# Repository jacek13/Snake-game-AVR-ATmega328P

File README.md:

# **Snake game on AVR**

The aim of my project was to create a device that allows you to play the popular game `"Snake"`. I completed the project as part of a university subject. While creating it, I used my original snake game written in C++ for Windows (graphics shown in the command line). I was prototyping the Arduino version. Then I rewritten the whole project into C language on the AVR microcontroller (ATmega328P). 

# **Game Demo**

# **Elements used in the project:**
* RGB matrix 8 x 8 WS2812B
* 5 microswitches
* Buzzer HCM1206X
* ATmega328P
* USB as power supply
* custom board (All eagle files is in resources folder)
* necessary RC elements (all information about values ​​is in the schematics)

# **PCB**

# **IMPORTANT**

in the resources folder there are hex files for both versions of the project (Arduino and AVR). Please note that the AVR version only works for frequencies based on the internal RC oscillator (Set fuse bits on 8Mhz). The prototype version from arduino uses an external crystal oscillator (then you have to change the fuse bits to the external 16 MHz clock). This limitation is due to the [**`light_ws2812`**](https://github.com/cpldcpu/light_ws2812) library that I am using in the project.

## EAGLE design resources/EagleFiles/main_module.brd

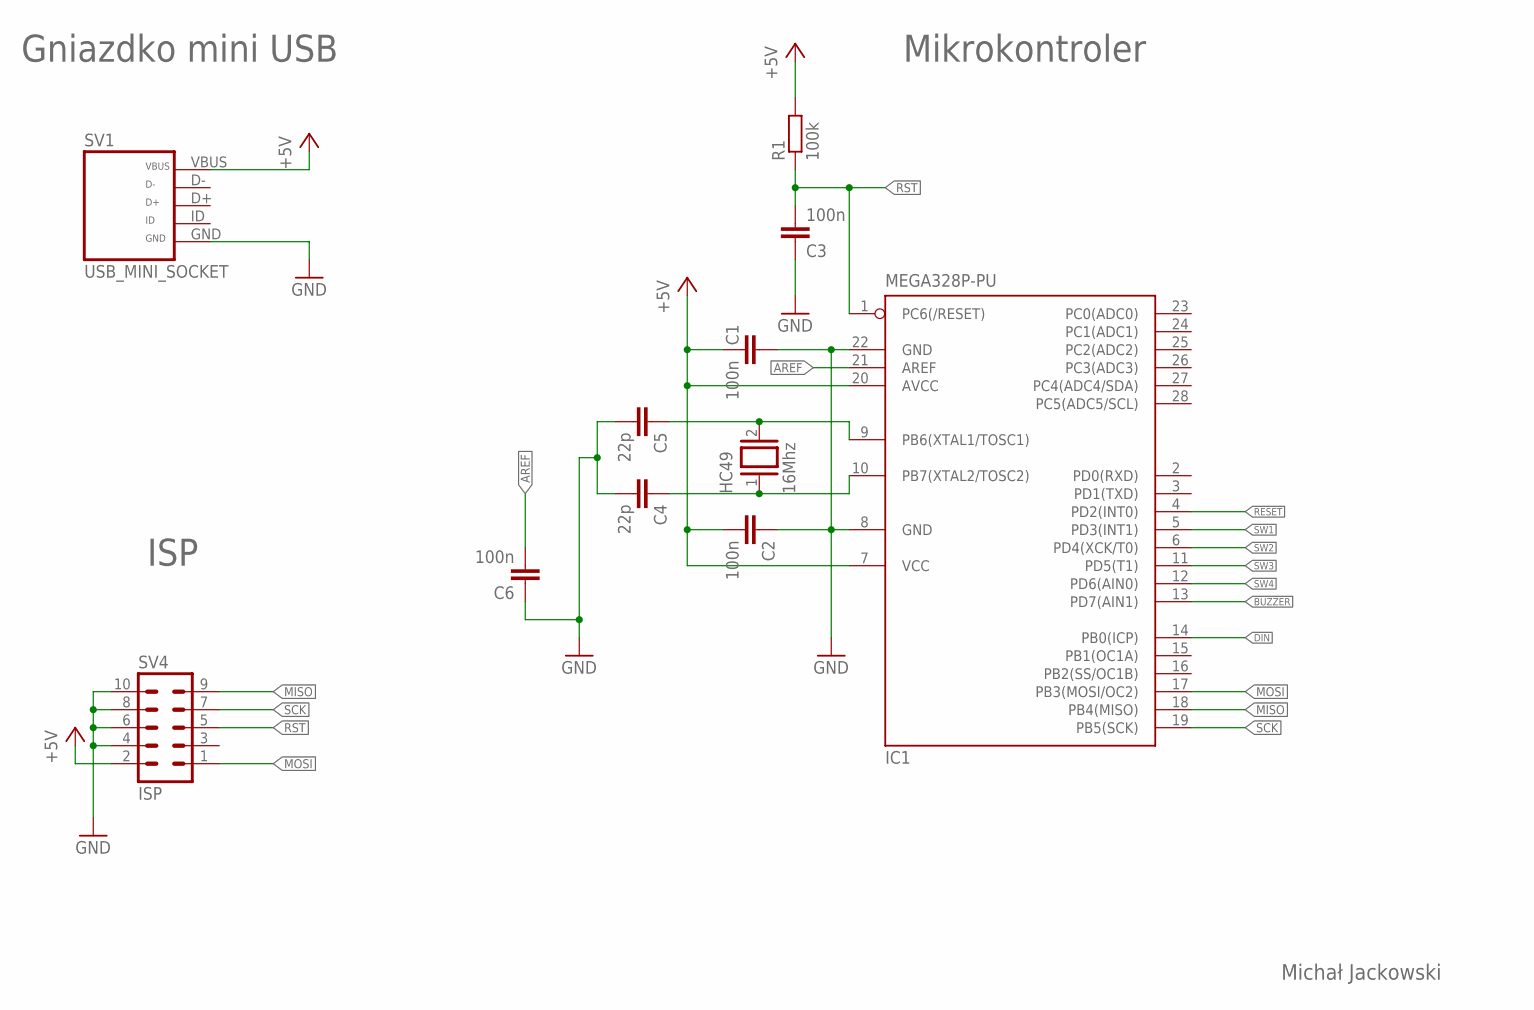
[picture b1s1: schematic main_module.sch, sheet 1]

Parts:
C1, C2, C3, C6: 100n; C025-040X050
C4, C5: 22p; C025-040X050
IC1: MEGA328P-PU; DIL28-3
Q1: 16Mhz; Q
R1: 100k; 0204/7
SV1: USB_MINI_SOCKET; FE05-1
SV4: ISP; ML10L

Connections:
+5V: C1.2, C2.2, IC1.7 (VCC), IC1.20 (AVCC), R1.2, SV1.VBUS, SV4.2; also elsewhere on the board
AREF: C6.2, IC1.21 (AREF)
BUZZER: IC1.13 (PD7(AIN1)); also elsewhere on the board
DIN: IC1.14 (PB0(ICP)); also elsewhere on the board
GND: C1.1, C2.1, C3.1, C4.2, C5.2, C6.1, IC1.8 (GND), IC1.22 (GND), SV1.GND, SV4.4, SV4.6, SV4.8, SV4.10; also elsewhere on the board
MISO: IC1.18 (PB4(MISO)), SV4.9
MOSI: IC1.17 (PB3(MOSI/OC2)), SV4.1
unnamed: C5.1, IC1.9 (PB6(XTAL1/TOSC1)), Q1.2
unnamed: C4.1, IC1.10 (PB7(XTAL2/TOSC2)), Q1.1
RESET: IC1.4 (PD2(INT0)); also elsewhere on the board
RST: C3.2, IC1.1 (PC6(/RESET)), R1.1, SV4.5
SCK: IC1.19 (PB5(SCK)), SV4.7
SW1: IC1.5 (PD3(INT1)); also elsewhere on the board
SW2: IC1.6 (PD4(XCK/T0)); also elsewhere on the board
SW3: IC1.11 (PD5(T1)); also elsewhere on the board
SW4: IC1.12 (PD6(AIN0)); also elsewhere on the board

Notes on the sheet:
Michał Jackowski
Gniazdko mini USB
ISP
Mikrokontroler

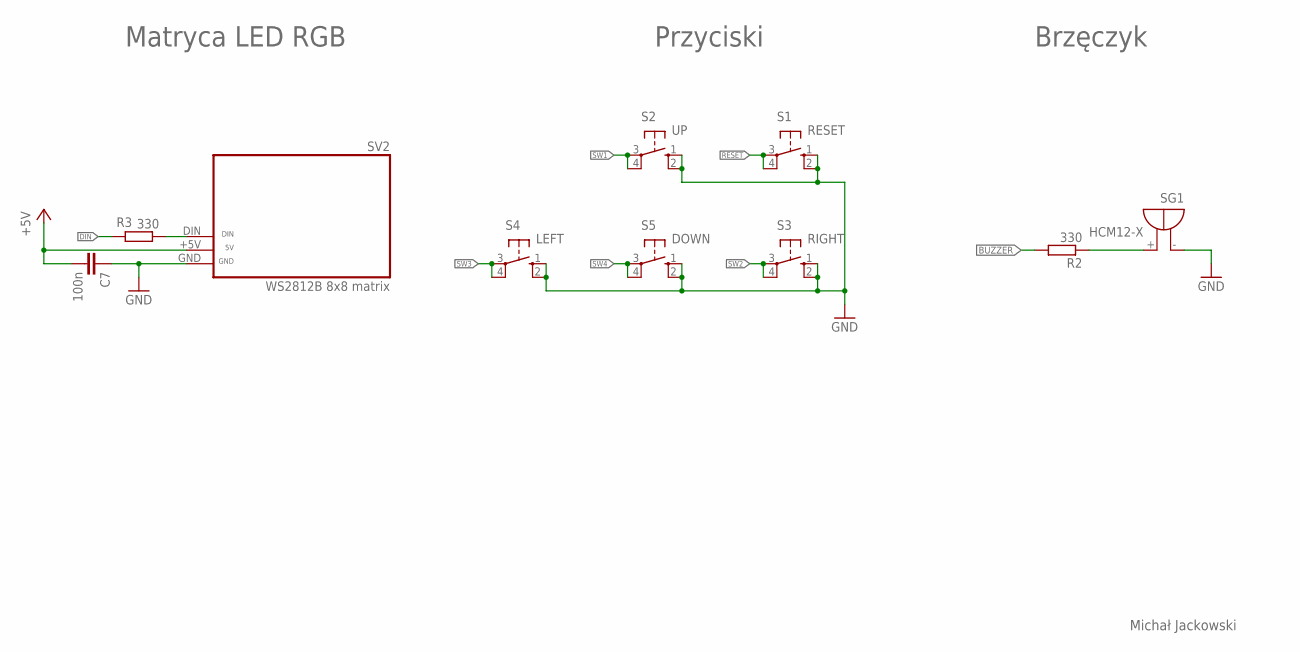
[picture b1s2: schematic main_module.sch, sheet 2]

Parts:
C7: 100n; C025-040X050
R2, R3: 330; 0204/7
S1: RESET; B3F-40XX
S2: UP; B3F-40XX
S3: RIGHT; B3F-40XX
S4: LEFT; B3F-40XX
S5: DOWN; B3F-40XX
SG1: HCM12-X; F/QMBIII
SV2: RGB_MATRIX_SOCKET; MA03-1

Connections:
+5V: C7.2, SV2.+5V (5V); also elsewhere on the board
BUZZER: R2.2; also elsewhere on the board
DIN: R3.2; also elsewhere on the board
GND: C7.1, S1.1 (S), S1.2 (S1), S2.1 (S), S2.2 (S1), S3.1 (S), S3.2 (S1), S4.1 (S), S4.2 (S1), S5.1 (S), S5.2 (S1), SG1.- (+), SV2.GND; also elsewhere on the board
unnamed: R2.1, SG1.+ (-)
unnamed: R3.1, SV2.DIN
RESET: S1.3, S1.4 (P1); also elsewhere on the board
SW1: S2.3, S2.4 (P1); also elsewhere on the board
SW2: S3.3, S3.4 (P1); also elsewhere on the board
SW3: S4.3, S4.4 (P1); also elsewhere on the board
SW4: S5.3, S5.4 (P1); also elsewhere on the board

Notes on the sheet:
Matryca LED RGB
Przyciski
Brzęczyk
Michał Jackowski

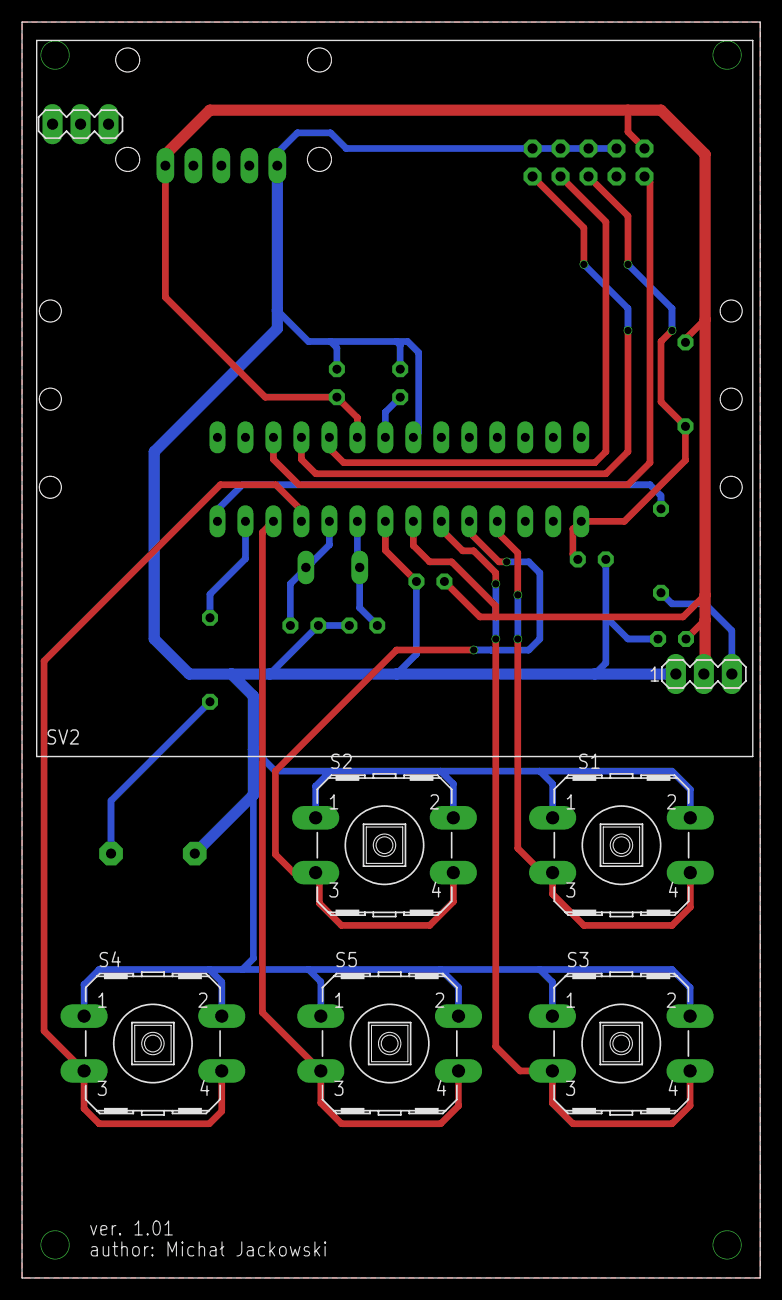
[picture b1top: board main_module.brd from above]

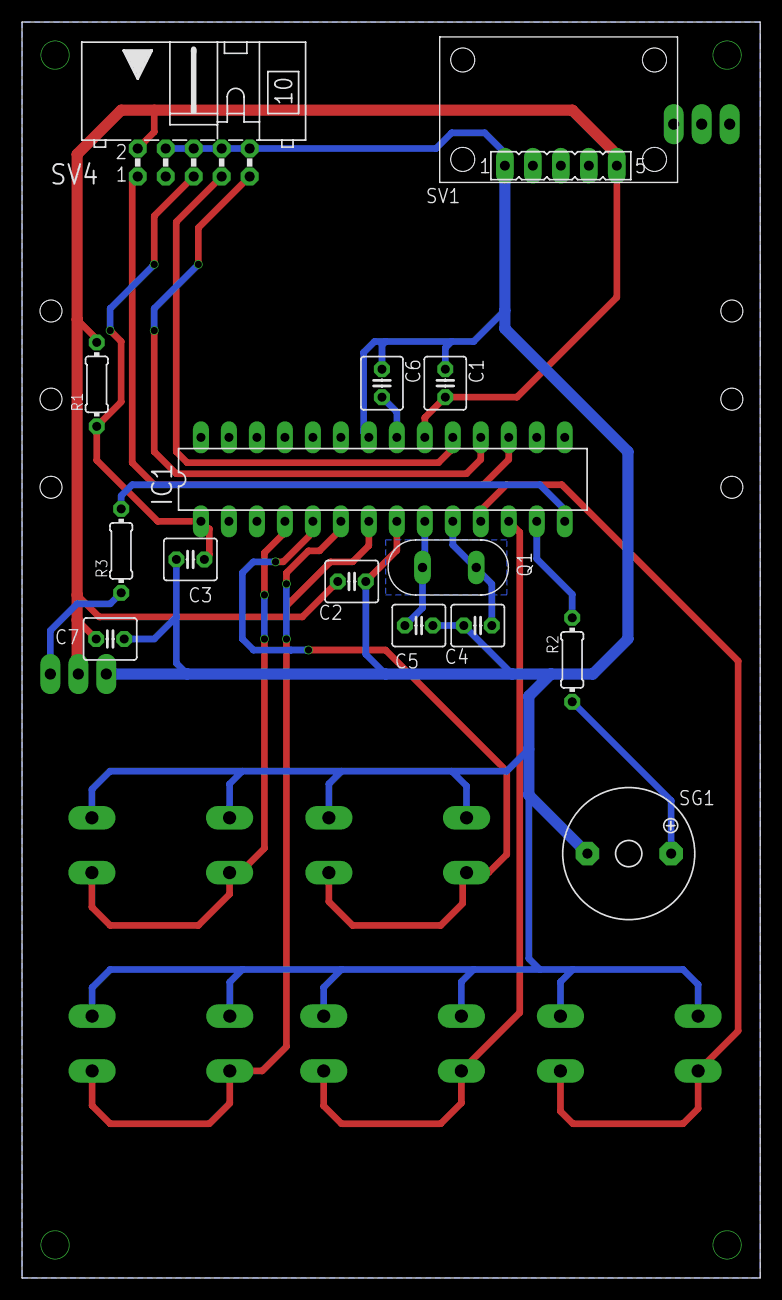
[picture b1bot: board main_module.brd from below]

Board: 2 copper layers, 67.0 x 114.0 mm, 21 parts (15 on the bottom side), 18 nets.

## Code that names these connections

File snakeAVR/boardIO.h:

/*
 * boardIO.h
 *
 * Created: 14.04.2022 20:01:20
 *  Author: Micha³ Jackowski
 */ 

#ifndef BOARDIO_H_
#define BOARDIO_H_

#include "structures.h"

#define PIN_BUZZER			(1 << PD7)
#define PIN_SWITCH_LEFT		(1 << PD5)
#define PIN_SWITCH_RIGHT	(1 << PD4)
#define PIN_SWITCH_UP		(1 << PD3)
#define PIN_SWITCH_DOWN		(1 << PD6)
#define PIN_GAME_RESET		(1 << PD2)
#define PIN_DATA_IN_DISPLAY (1 << PB0)

#define BUZZER_ON PORTD	 |= PIN_BUZZER
#define BUZZER_OFF PORTD &= ~PIN_BUZZER
#define BUZZER_TOG PORTD ^= PIN_BUZZER

void initRegisters();

GAME_LOGIC read_from_inputs(GAME_LOGIC previous_direction);

void generate_sound(int8_t _scored, int8_t _game_over);

#endif /* BOARDIO_H_ */

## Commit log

2022-04-14 fill repo
2022-04-14 Readme update
2022-04-14 update readme YT link
2022-04-14 add eagle files
